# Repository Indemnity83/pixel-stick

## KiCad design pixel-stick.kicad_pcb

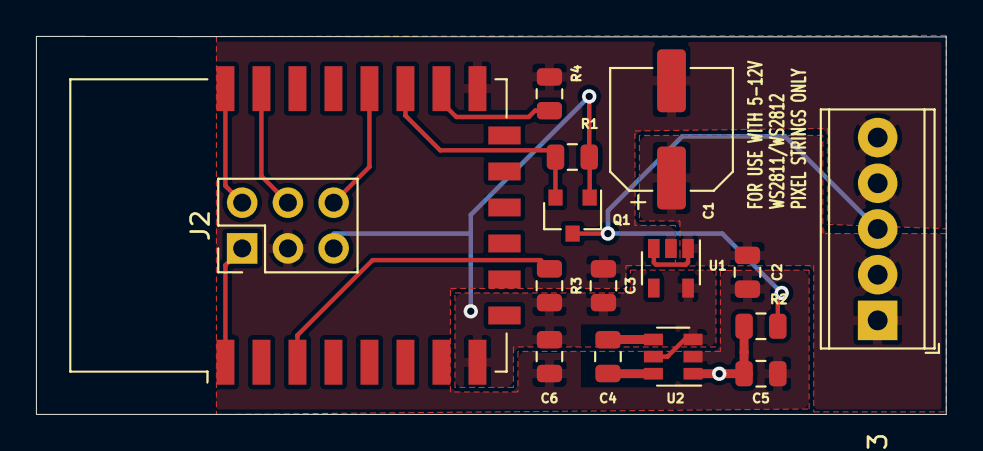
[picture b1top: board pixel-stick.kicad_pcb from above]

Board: 2 copper layers, 50.5 x 21.0 mm, 16 parts (0 on the bottom side), 14 nets.

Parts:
C1: 100µF; CP_Elec_6.3x7.7
C2: 10µF 16V; C_0805_2012Metric
C3, C5, C6: 10µF; C_0805_2012Metric
C4: 1µF; C_0805_2012Metric
J2: Conn_02x03_Counter_Clockwise; PinHeader_2x03_P2.54mm_Vertical
J3: Screw_Terminal_01x05; TerminalBlock_Phoenix_MPT-0,5-5-2.54_1x05_P2.54mm_Horizontal
Q1: BSS138; SOT-23
R1, R2, R3, R4: 10k; R_0805_2012Metric
U1: SPX3819M5-L-3-3; SOT-23-5
U2: RT9361AGE; SOT-23-6
U3: ESP-12E

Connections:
+3V3: C3.1, C6.1, J2.5, Q1.1, R1.1, R3.1, U1.5, U2.3, U2.5, U3.8
+5V: C5.1, R2.1, U2.1
/DATA: J3.3, Q1.3, R2.2
/EN: R3.2, U3.3
/GPIO0: J2.6, U3.18
/GPIO2: Q1.2, R1.2, U3.17
/GPIO15: R4.1, U3.16
/RXD: J2.4, U3.21
/TXD: J2.2, U3.22
/~RST: J2.1, U3.1
GND: C1.2, C2.2, C3.2, C5.2, C6.2, J2.3, J3.4, J3.5, R4.2, U1.2, U2.2, U3.15
unnamed: C4.1, U2.6
unnamed: C4.2, U2.4
VIN: C1.1, C2.1, J3.1, J3.2, U1.1, U1.3

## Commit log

2019-12-06 Initial Design
2019-12-06 use fills for power
2019-12-06 include gerbers
2019-12-06 cleanup flooded planes
2019-12-06 improve decoupling cap placement for ESP
2019-12-06 address DRC errors
2019-12-06 consilidate parts on pcb
2019-12-06 more layer cleanup
2019-12-06 include board images
2019-12-06 more power/gnd plane cleanup
2019-12-06 improve current flow
2019-12-06 fix drc errors
2019-12-06 removed paralell and adjacent caps
2019-12-06 add power led
2019-12-06 remove programming features
2019-12-06 cleanup silkscreen layer
2019-12-06 update silkscreen
2019-12-07 transistor based level shifting
2019-12-07 replace logic chip with simple buffer
2019-12-07 increase passives to 1206 footprint
2019-12-08 cleanup
2019-12-11 make it tiny
2019-12-16 make custom vin power symbol
2019-12-16 make it tiny, based on simple blocks
2019-12-16 fix library symbols
2019-12-17 add esp module
2019-12-17 layout board with ESP-M2
2019-12-17 include esp8285 libraries
2019-12-17 fix footprint library path
2019-12-17 use jst-ph connector
    populating the connector is optional, the pads can be used for either direct solder wires or for a jst-ph to jst-sm adapter
2019-12-17 generate assets
2019-12-17 update board version
2019-12-17 Use ESP-M2 Module
2019-12-17 increase vin trace width
2019-12-18 trim excess pcb
2019-12-19 make design work for ESP-01 or ESP-M2
2019-12-19 remove resistor from GPIO2 pull-up
    may have been a bad idea ... will need to check that things still work. Its possible the ESP-01 and ESP-M2 have internal pull ups alredy enabled and I can remove the external 3V3 entirely.
2019-12-20 create visual-diff action
2019-12-20 remove incorrect repo from checkout
2019-12-20 tag files for clean and smudge
    see: https://jnavila.github.io/plotkicadsch/
2019-12-20 generate visual diff
2019-12-20 install plotgitsch
2019-12-20 update shell after installing plotkicadsch
2019-12-20 draw a full board instead
2019-12-20 use checkout v1
2019-12-20 Add R3 back to GPIO2
    Also re-laid out the microcontrollers in schematic to make it clearer how the common interface is achieved.
2019-12-21 simplify programming
    pull the buttons and all pins necessary off the board. A programming adapter will need to be made.
2019-12-21 remove buttons from schematic
2019-12-27 add pull-up for reset and enable
2019-12-27 upgrade 3.3v regulator
2019-12-28 consolidate capacitors
2020-01-08 level shift with fet instead of buffer
2020-01-08 add pull-up resistor on enable
2020-01-08 improve input filtering
    remove the fuse and increase the bulk decoupling cap
2020-01-08 add esp-12 module
    allow populating either an ESP-01 or ESP-12 module
2020-01-08 add a programming header
    will require a secondary board with reset and prog buttons to flash chips.
2020-01-09 Fix libraries and symbols
2020-01-09 purge generated files
2020-01-09 first-pass at layout
2020-01-10 Layout board
2020-01-10 revise board for testing
    use the ESP-01 socket for most test points, added a 5V test point and changed the wire solder pads for 2.54mm pitch. Also added mounting (guide) holes for a test jig
2020-01-11 move 5v test pad to back of board
2020-01-11 shrink board
2020-01-11 rev 2.0a
2021-02-08 utilize level shifter
